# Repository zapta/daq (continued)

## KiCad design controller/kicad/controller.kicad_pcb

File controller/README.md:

# Data Acquisition - Controller board.

| :warning: WARNING                                               |
| :-------------------------------------------------------------- |
| This design is an unverified work in progress (as of May 2023). |

## Overview

This plugin board contains the microcontroller that controls the system and communicates with the host PC. It is based on the WeAct Studio STM32H750 module, and future version may have the STM32H750 MCU directly on the board.

## Design decisions

* All the MCU signals are routed to the bus, to provide flexibility and future system expansion.
* All signals are protected against ESD using TVS diodes.
* Controller can be powered from the bus or from the USB port, with power arbitration using OR'ed diodes. The USB power does not power the bus to avoid overloading the host computer.
* The WeAct module can be soldered to the board using pin header or can be removable using a set of male/female headers.

## Board dimensions

## BOM

Key components:

* WeAct Studio [STM32H750 module](https://github.com/WeActStudio/MiniSTM32H7xx).

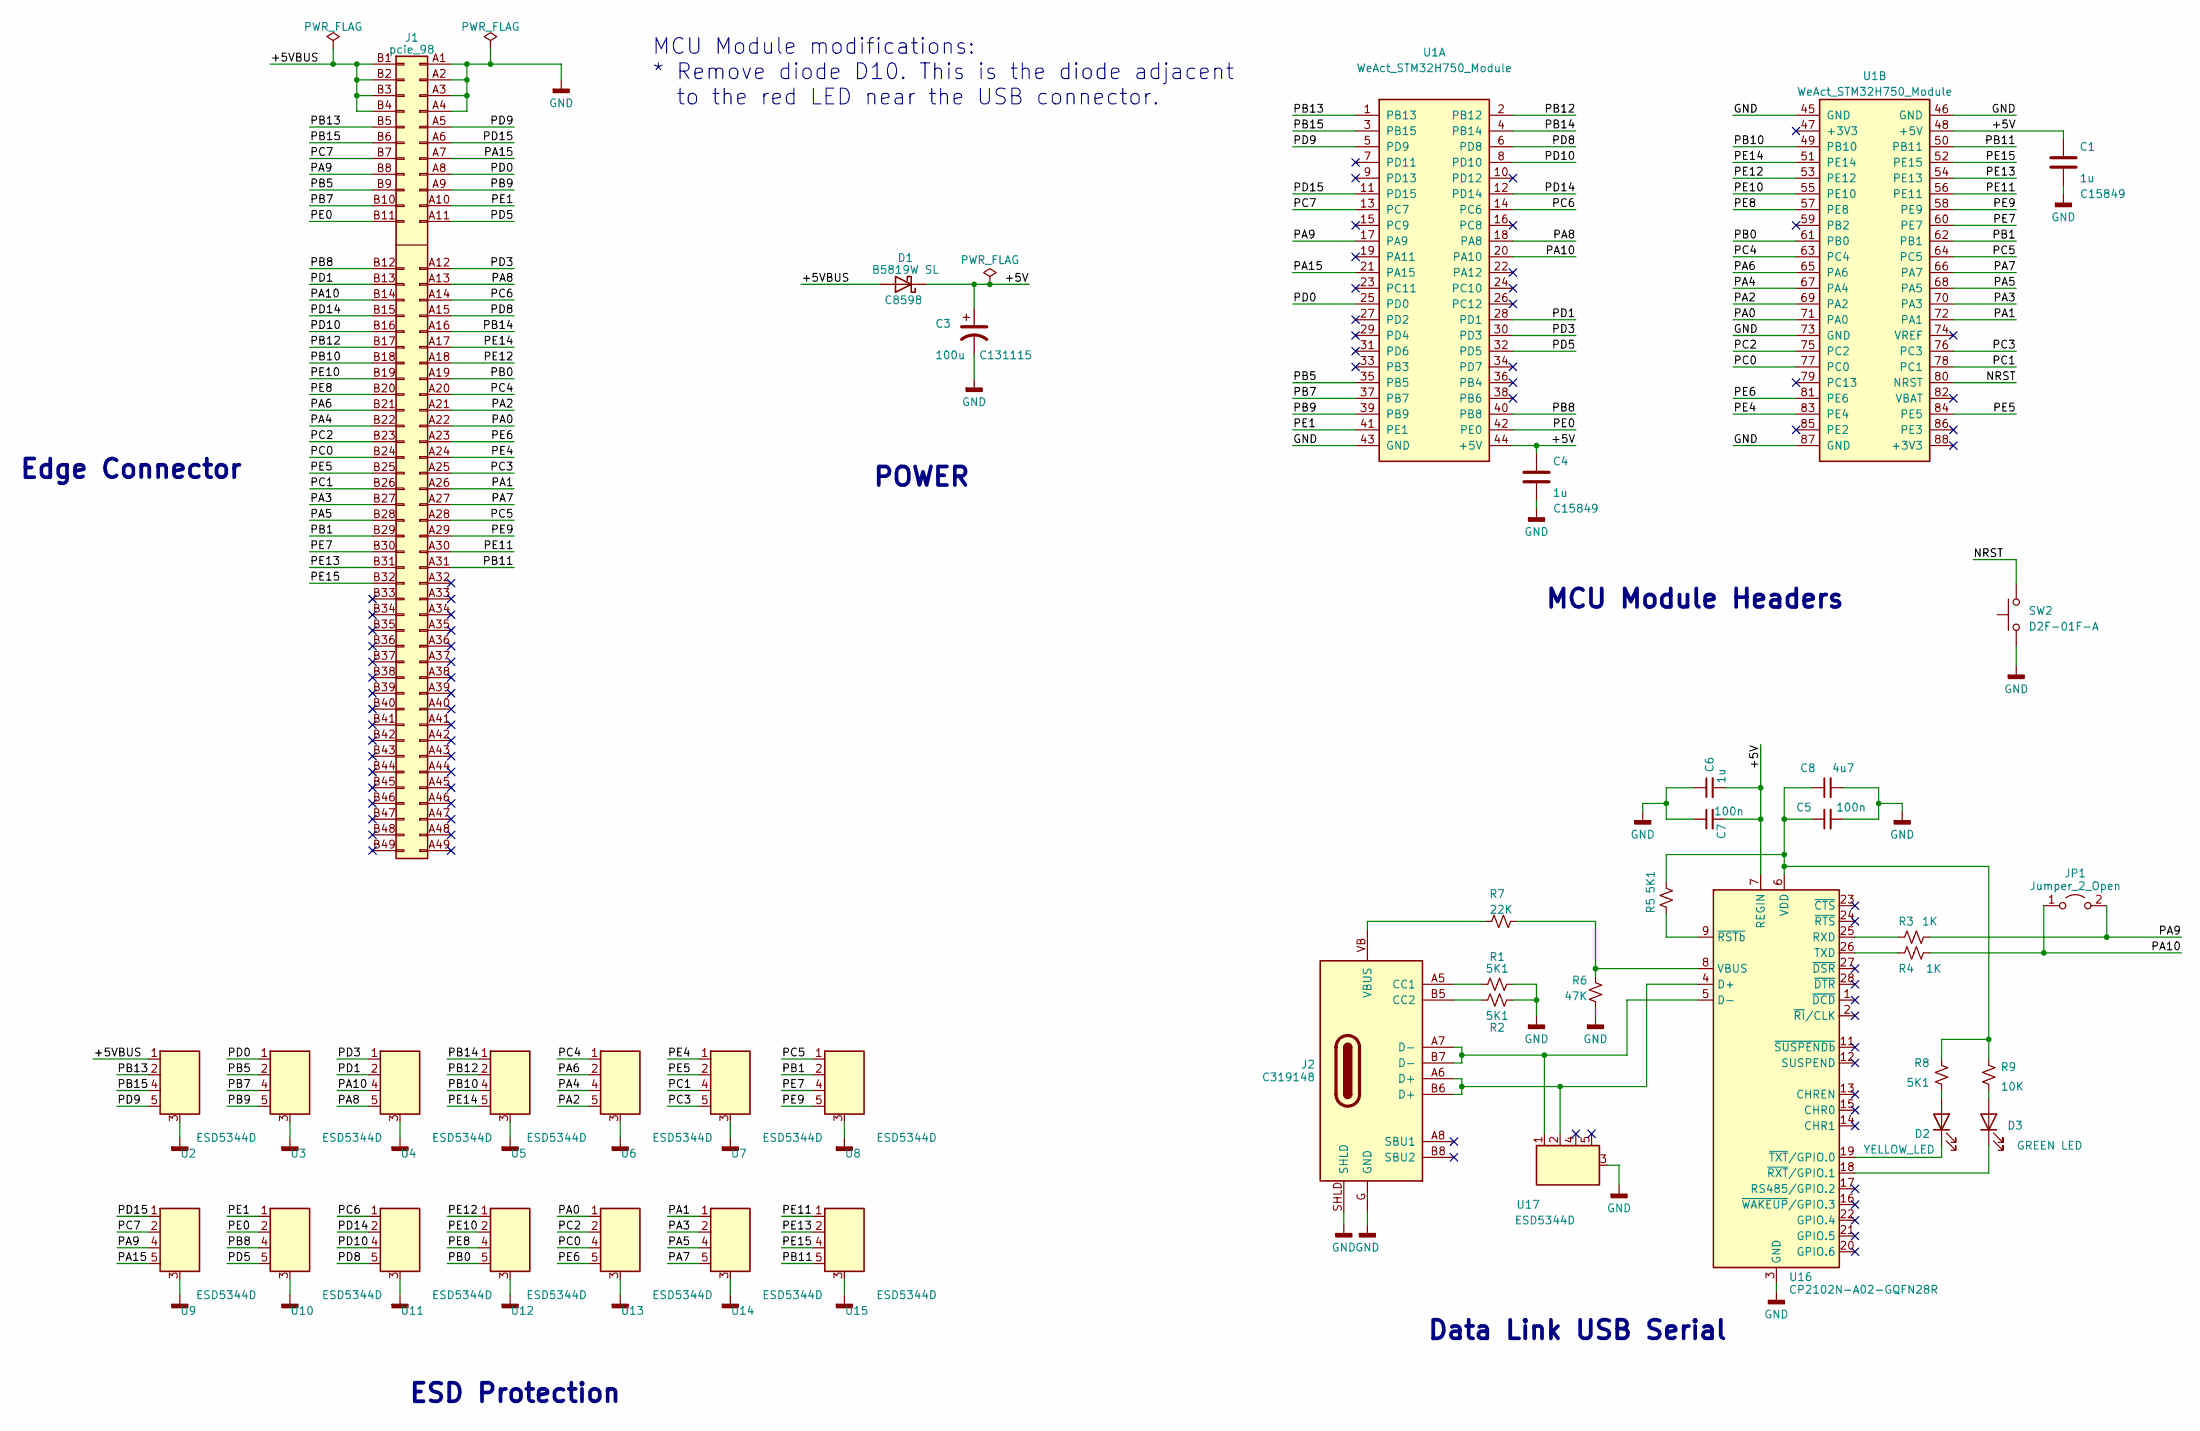
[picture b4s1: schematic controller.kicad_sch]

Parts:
C1, C4, C6: 1u; C_0603_1608Metric; LCSC C15849
C3: 100u; CP_Elec_5x5.4_JLCPCB; LCSC C131115
C5, C7: 100n; C_0603_1608Metric; LCSC C14663
C8: 4u7; C_0603_1608Metric; LCSC C19666
D1: B5819W SL; D_SOD-123; LCSC C8598
D2: YELLOW_LED; LED_0603_1608Metric; LCSC C72038
D3: GREEN LED; LED_0603_1608Metric; LCSC C72043
J1: pcie_98; PCIE_98_CARD; LCSC DNP
J2: USB_C_Receptacle_USB2.0; USB_C_Receptacle_XKB_U262-16XN-4BVC11; LCSC C319148
JP1: Jumper_2_Open; PinHeader_1x02_P2.54mm_Vertical; LCSC DNP
R1, R2, R5, R8: 5K1; R_0603_1608Metric; LCSC C23186
R3, R4: 1K; R_0603_1608Metric; LCSC C21190
R6: 47K; R_0603_1608Metric; LCSC C25819
R7: 22K; R_0603_1608Metric; LCSC C31850
R9: 10K; R_0603_1608Metric; LCSC C25804
SW2: D2F-01F-A; microswitch; LCSC C726013
U1: WeAct_STM32H750_Module; weact_stm32fh750; LCSC DNP
U2, U3, U4, U5, U6, U7, U8, U9, U10, U11, U12, U13, U14, U15, U17: ESD5344D; Diodes_UDFN-10_1.0x2.5mm_P0.5mm; LCSC C2841840
U16: CP2102N-A02-GQFN28R; QFN-28-1EP_5x5mm_P0.5mm_EP3.35x3.35mm; LCSC C964632

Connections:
/+5V: C1.1, C3.1, C4.1, C6.2, C7.2, D1.1 (K), U1.44 (+5V), U1.48 (+5V), U16.7 (REGIN)
/+5VBUS: D1.2 (A), J1.B1 (Pin_b1), J1.B2 (Pin_b2), J1.B3 (Pin_b3), J1.B4 (Pin_b4), U2.1 (D1)
/NRST: SW2.2, U1.80 (NRST)
/PA0: J1.A22 (Pin_a22), U1.71 (PA0), U13.1 (D1)
/PA1: J1.A26 (Pin_a26), U1.72 (PA1), U14.1 (D1)
/PA2: J1.A21 (Pin_a21), U1.69 (PA2), U6.5 (D4)
/PA3: J1.B27 (Pin_b27), U1.70 (PA3), U14.2 (D2)
/PA4: J1.B22 (Pin_b22), U1.67 (PA4), U6.4 (D3)
/PA5: J1.B28 (Pin_b28), U1.68 (PA5), U14.4 (D3)
/PA6: J1.B21 (Pin_b21), U1.65 (PA6), U6.2 (D2)
/PA7: J1.A27 (Pin_a27), U1.66 (PA7), U14.5 (D4)
/PA8: J1.A13 (Pin_a13), U1.18 (PA8), U4.5 (D4)
/PA9: J1.B8 (Pin_b8), JP1.2 (B), R3.2, U1.17 (PA9), U9.4 (D3)
/PA10: J1.B14 (Pin_b14), JP1.1 (A), R4.2, U1.20 (PA10), U4.4 (D3)
/PA15: J1.A7 (Pin_a7), U1.21 (PA15), U9.5 (D4)
/PB0: J1.A19 (Pin_a19), U1.61 (PB0), U12.5 (D4)
/PB1: J1.B29 (Pin_b29), U1.62 (PB1), U8.2 (D2)
/PB5: J1.B9 (Pin_b9), U1.35 (PB5), U3.2 (D2)
/PB7: J1.B10 (Pin_b10), U1.37 (PB7), U3.4 (D3)
/PB8: J1.B12 (Pin_b12), U1.40 (PB8), U10.4 (D3)
/PB9: J1.A9 (Pin_a9), U1.39 (PB9), U3.5 (D4)
/PB10: J1.B18 (Pin_b18), U1.49 (PB10), U5.4 (D3)
/PB11: J1.A31 (Pin_a31), U1.50 (PB11), U15.5 (D4)
/PB12: J1.B17 (Pin_b17), U1.2 (PB12), U5.2 (D2)
/PB13: J1.B5 (Pin_b5), U1.1 (PB13), U2.2 (D2)
/PB14: J1.A16 (Pin_a16), U1.4 (PB14), U5.1 (D1)
/PB15: J1.B6 (Pin_b6), U1.3 (PB15), U2.4 (D3)
/PC0: J1.B24 (Pin_b24), U1.77 (PC0), U13.4 (D3)
/PC1: J1.B26 (Pin_b26), U1.78 (PC1), U7.4 (D3)
/PC2: J1.B23 (Pin_b23), U1.75 (PC2), U13.2 (D2)
/PC3: J1.A25 (Pin_a25), U1.76 (PC3), U7.5 (D4)
/PC4: J1.A20 (Pin_a20), U1.63 (PC4), U6.1 (D1)
/PC5: J1.A28 (Pin_a28), U1.64 (PC5), U8.1 (D1)
/PC6: J1.A14 (Pin_a14), U1.14 (PC6), U11.1 (D1)
/PC7: J1.B7 (Pin_b7), U1.13 (PC7), U9.2 (D2)
/PD0: J1.A8 (Pin_a8), U1.25 (PD0), U3.1 (D1)
/PD1: J1.B13 (Pin_b13), U1.28 (PD1), U4.2 (D2)
/PD3: J1.A12 (Pin_a12), U1.30 (PD3), U4.1 (D1)
/PD5: J1.A11, U1.32 (PD5), U10.5 (D4)
/PD8: J1.A15 (Pin_a15), U1.6 (PD8), U11.5 (D4)
/PD9: J1.A5 (Pin_a5), U1.5 (PD9), U2.5 (D4)
/PD10: J1.B16 (Pin_b16), U1.8 (PD10), U11.4 (D3)
/PD14: J1.B15 (Pin_b15), U1.12 (PD14), U11.2 (D2)
/PD15: J1.A6 (Pin_a6), U1.11 (PD15), U9.1 (D1)
/PE0: J1.B11 (Pin_b11), U1.42 (PE0), U10.2 (D2)
/PE1: J1.A10 (Pin_a10), U1.41 (PE1), U10.1 (D1)
/PE4: J1.A24 (Pin_a24), U1.83 (PE4), U7.1 (D1)
/PE5: J1.B25 (Pin_b25), U1.84 (PE5), U7.2 (D2)
/PE6: J1.A23 (Pin_a23), U1.81 (PE6), U13.5 (D4)
/PE7: J1.B30 (Pin_b30), U1.60 (PE7), U8.4 (D3)
/PE8: J1.B20 (Pin_b20), U1.57 (PE8), U12.4 (D3)
/PE9: J1.A29 (Pin_a29), U1.58 (PE9), U8.5 (D4)
/PE10: J1.B19 (Pin_b19), U1.55 (PE10), U12.2 (D2)
/PE11: J1.A30 (Pin_a30), U1.56 (PE11), U15.1 (D1)
/PE12: J1.A18 (Pin_a18), U1.53 (PE12), U12.1 (D1)
/PE13: J1.B31 (Pin_b31), U1.54 (PE13), U15.2 (D2)
/PE14: J1.A17 (Pin_a17), U1.51 (PE14), U5.5 (D4)
/PE15: J1.B32 (Pin_b32), U1.52 (PE15), U15.4 (D3)
GND: C1.2, C3.2, C4.2, C5.2, C6.1, C7.1, C8.2, J1.A1 (Pin_a1), J1.A2 (Pin_a2), J1.A3 (Pin_a3), J1.A4 (Pin_a4), J2.G (GND), J2.SHLD, R1.2, R2.2, R6.1, SW2.1, U1.43 (GND), U1.45 (GND), U1.46 (GND), U1.73 (GND), U1.87 (GND), U2.3 (GND), U3.3 (GND), U4.3 (GND), U5.3 (GND), U6.3 (GND), U7.3 (GND), U8.3 (GND), U9.3 (GND), U10.3 (GND), U11.3 (GND), U12.3 (GND), U13.3 (GND), U14.3 (GND), U15.3 (GND), U16.3 (GND), U16.29 (GND), U17.3 (GND)
unnamed: D2.2 (A), R8.1
unnamed: D2.1 (K), U16.19 (~TXT/GPIO.0)
unnamed: D3.2 (A), R9.1
unnamed: D3.1 (K), U16.18 (~RXT/GPIO.1)
unnamed: J2.A5 (CC1), R1.1
unnamed: J2.B5 (CC2), R2.1
unnamed: J2.VB (VBUS), R7.2
unnamed: J2.A6 (D+), J2.B6 (D+), U16.4 (D+), U17.2 (D2)
unnamed: J2.A7 (D-), J2.B7 (D-), U16.5 (D-), U17.1 (D1)
unnamed: R3.1, U16.25 (RXD)
unnamed: R4.1, U16.26 (TXD)
unnamed: R6.2, R7.1, U16.8 (VBUS)
unnamed: C5.1, C8.1, R5.2, R8.2, R9.2, U16.6 (VDD)
unnamed: R5.1, U16.9 (~RSTb)

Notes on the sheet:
ESD Protection
MCU Module Headers
Data Link USB Serial
Edge Connector
POWER
MCU Module modifications: * Remove diode D10. This is the diode adjacent to the red LED near the USB connector.

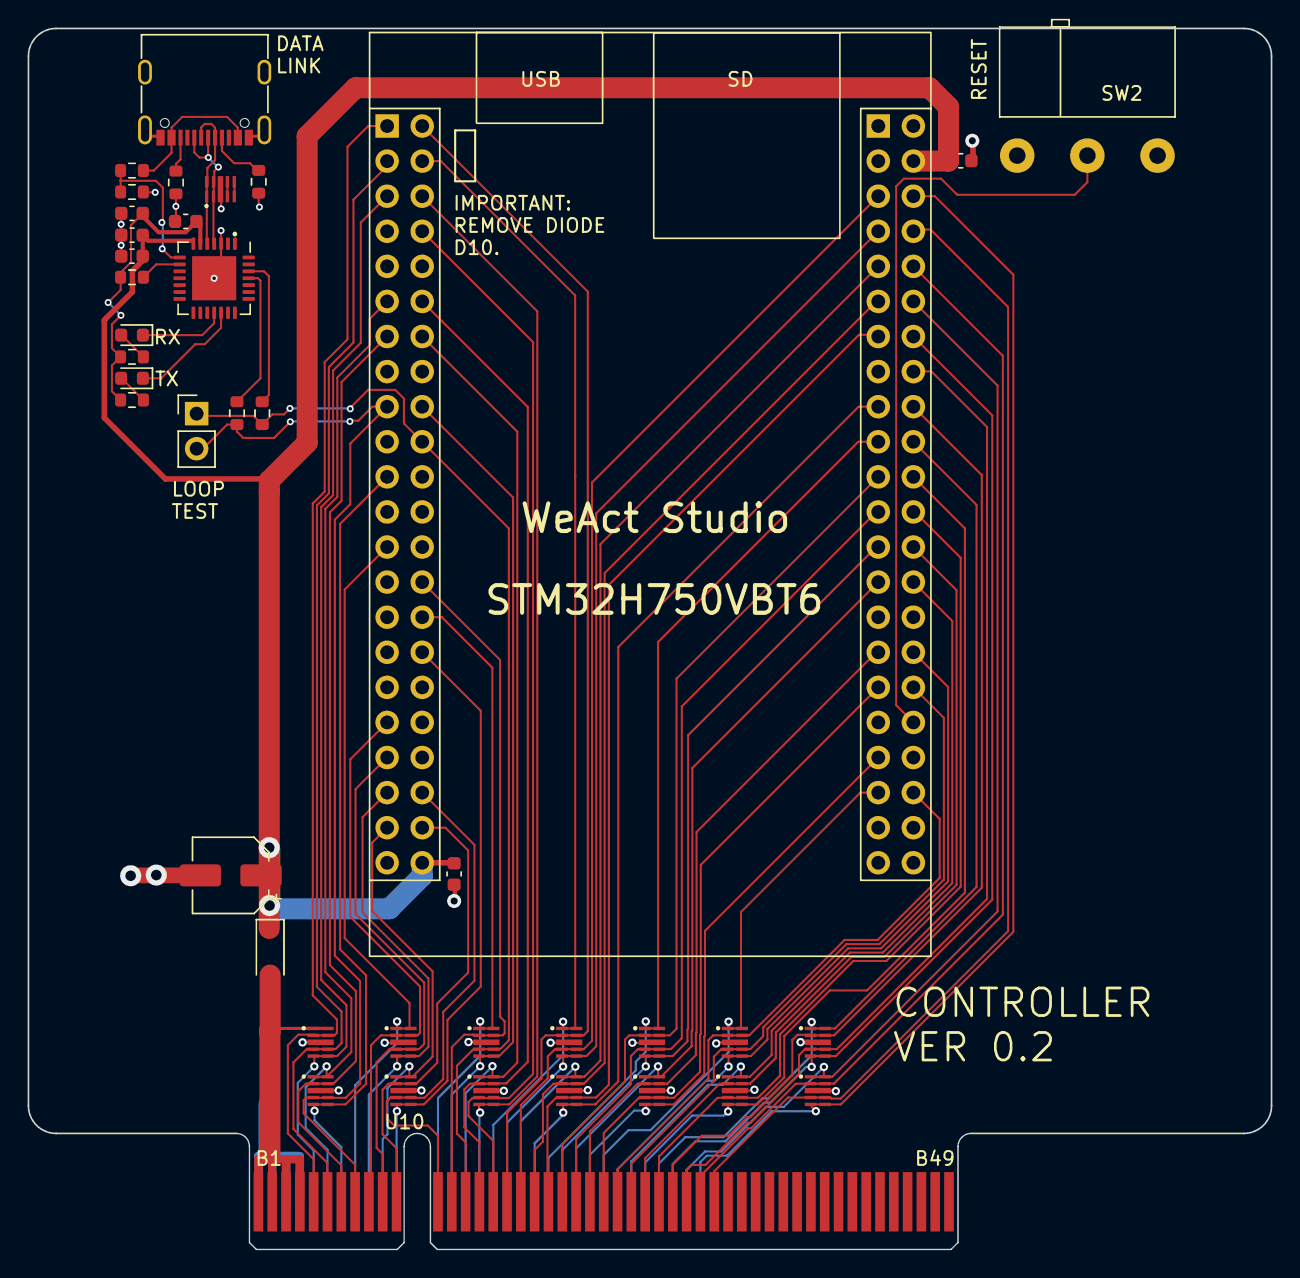
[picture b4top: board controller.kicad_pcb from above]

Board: 2 copper layers, 90.0 x 88.4 mm, 40 parts (0 on the bottom side), 73 nets.

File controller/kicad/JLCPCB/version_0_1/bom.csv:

Designator,Footprint,Quantity,Value,LCSC Part #
"C1, C4, C6",0603,3,1u,C15849
"C2, C3",CP_Elec_5x5.4_JLCPCB,2,100u,C131115
"C5, C7",0603,2,100n,C14663
C8,0603,1,4u7,C19666
D1,D_SOD-123,1,B5819W SL,C8598
J1,PCIE_98_CARD,1,pcie_98,DNP
J2,USB_C_Receptacle_XKB_U262-16XN-4BVC11,1,USB_C_Receptacle_USB2.0,C319148
JP1,PinHeader_1x02_P2.54mm_Vertical,1,Jumper_2_Open,DNP
"R1, R2, R5",0603,3,5K1,C23186
"R3, R4",0603,2,1K,C21190
U1,weact_stm32fh750,1,WeAct_STM32H750_Module,DNP
"U10, U11, U12, U13, U14, U15, U2, U3, U4, U5, U6, U7, U8, U9",Diodes_UDFN-10_1.0x2.5mm_P0.5mm,14,ESD5344D,C2841840
U16,QFN-28-1EP_5x5mm_P0.5mm_EP3.35x3.35mm,1,CP2102N-A01-GQFN28-Interface_USB,C6568

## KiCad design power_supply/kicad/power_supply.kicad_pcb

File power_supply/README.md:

# Data Acquisition - Power Supply board.

| :warning: WARNING|
|:---|
| This design is an unverified work in progress (as of May 2023).|

## Overview

This plugin board contains an DC/DC module which generates the 5VCD feed of the bus from the 12-24V DC input.

## Design decisions

* The power supply is isolated such that VIN is not galvanically connected to the system.
* Can provide 5V @ 2A from 9-36VDC input.
* Contains fuses on input and output voltages and ESD protection on the 5V output voltage.
* Contains indication LEDs for input and output voltages.
* Contains test points for input and output voltages.
* Inexpensive 2 layers PCB design with one layer dedicated for ground plane.
* Not intended for hot swapping.

## Board dimensions

Identical to the controller board.

## BOM

* URB2405YMD-10WR3 DC/DC module. Available from several vendors, with  
Mornsun being the canonical one.

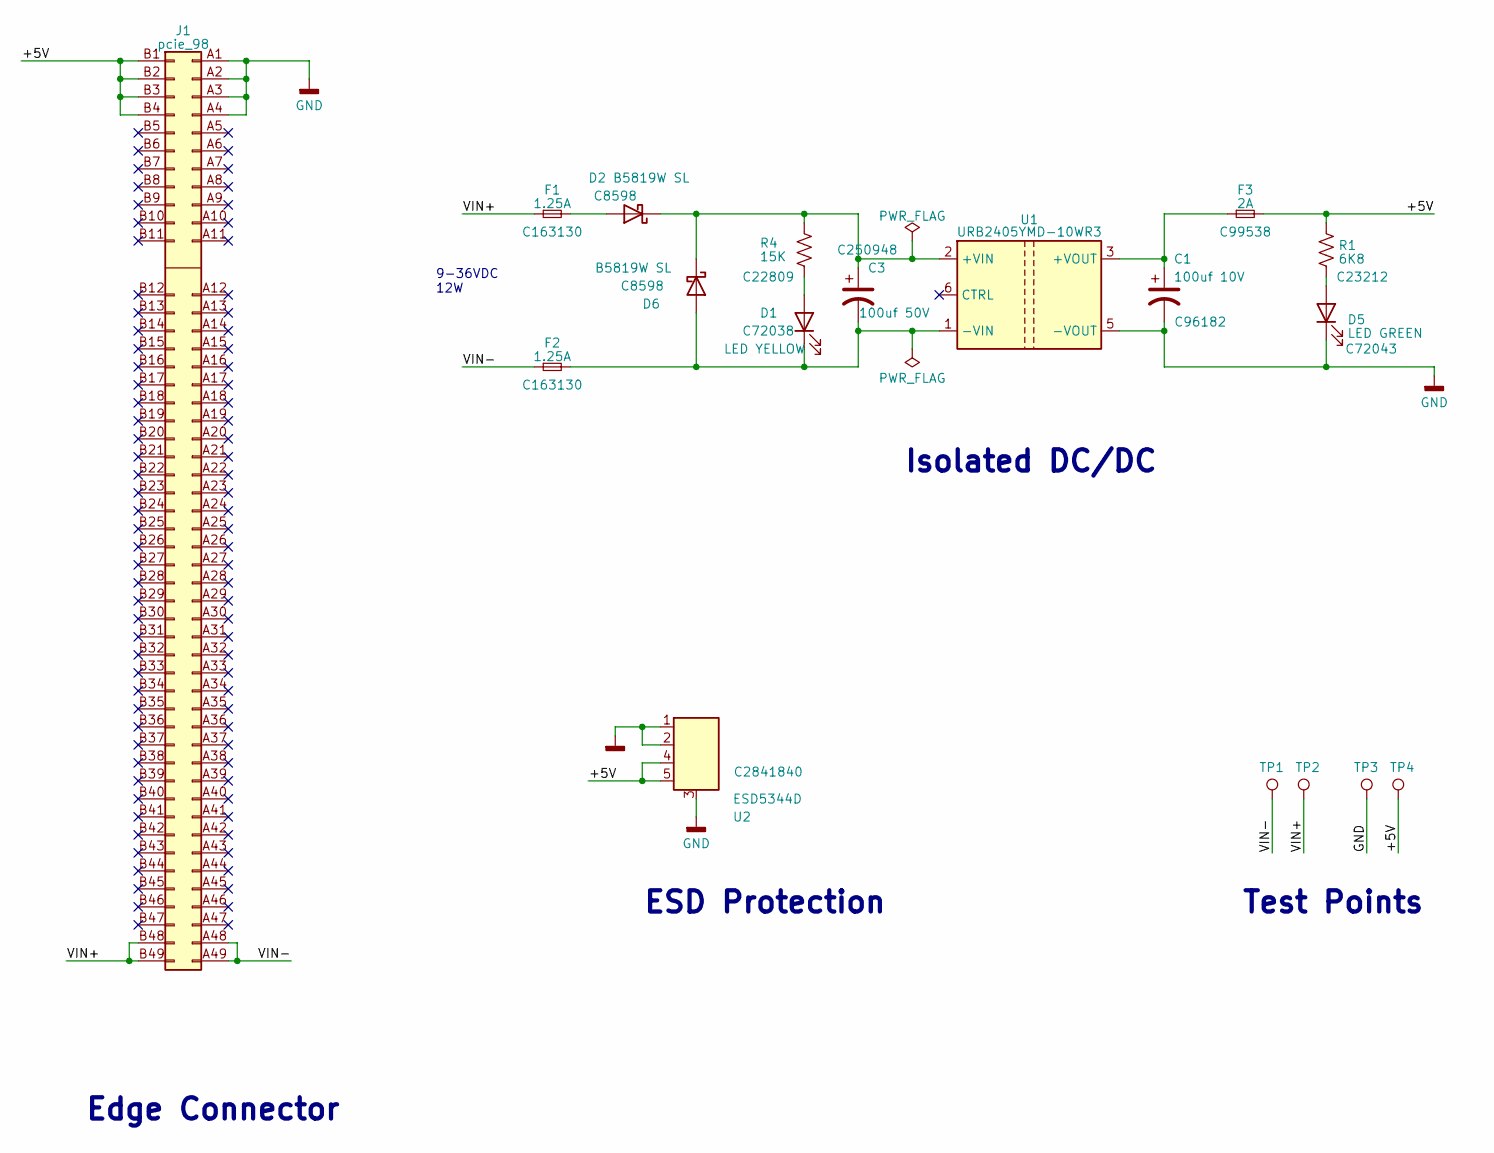
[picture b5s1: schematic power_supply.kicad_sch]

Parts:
C1: 100uf 10V; CP_Elec_5x5.4; LCSC C96182
C3: 100uf 50V; C_Elec_8x10.2; LCSC C250948
D1: LED YELLOW; LED_0603_1608Metric; LCSC C72038
D2, D6: B5819W SL; D_SOD-123; LCSC C8598
D5: LED GREEN; LED_0603_1608Metric; LCSC C72043
F1, F2: 1.25A; Fuse_1206_3216Metric_Pad1.42x1.75mm_HandSolder; LCSC C163130
F3: 2A; Fuse_1206_3216Metric_Pad1.42x1.75mm_HandSolder; LCSC C99538
J1: pcie_98; PCIE_98_CARD; LCSC DNP
R1: 6K8; R_0603_1608Metric; LCSC C23212
R4: 15K; R_0603_1608Metric; LCSC C22809
TP1, TP2, TP3, TP4: TestPoint; Test_Pad; LCSC DNP
U1: URB2405YMD-10WR3; DCDC; LCSC C91825
U2: ESD5344D; Diodes_UDFN-10_1.0x2.5mm_P0.5mm; LCSC C2841840

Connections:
/+5V: F3.2, J1.B1 (Pin_b1), J1.B2 (Pin_b2), J1.B3 (Pin_b3), J1.B4 (Pin_b4), R1.1, TP4.1, U2.4 (D3), U2.5 (D4)
/VIN+: F1.1, J1.B48 (Pin_b48), J1.B49 (Pin_b49), TP2.1
/VIN-: F2.1, J1.A48 (Pin_a48), J1.A49 (Pin_a49), TP1.1
GND: C1.2, D5.1 (K), J1.A1 (Pin_a1), J1.A2 (Pin_a2), J1.A3 (Pin_a3), J1.A4 (Pin_a4), TP3.1, U1.5 (-VOUT), U2.1 (D1), U2.2 (D2), U2.3 (GND)
unnamed: D1.2 (A), R4.2
unnamed: C3.2, D1.1 (K), D6.2 (A), F2.2, U1.1 (-VIN)
unnamed: D2.2 (A), F1.2
unnamed: C3.1, D2.1 (K), D6.1 (K), R4.1, U1.2 (+VIN)
unnamed: D5.2 (A), R1.2
unnamed: C1.1, F3.1, U1.3 (+VOUT)

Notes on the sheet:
ESD Protection
9-36VDC 12W
Edge Connector
Isolated DC/DC
Test Points

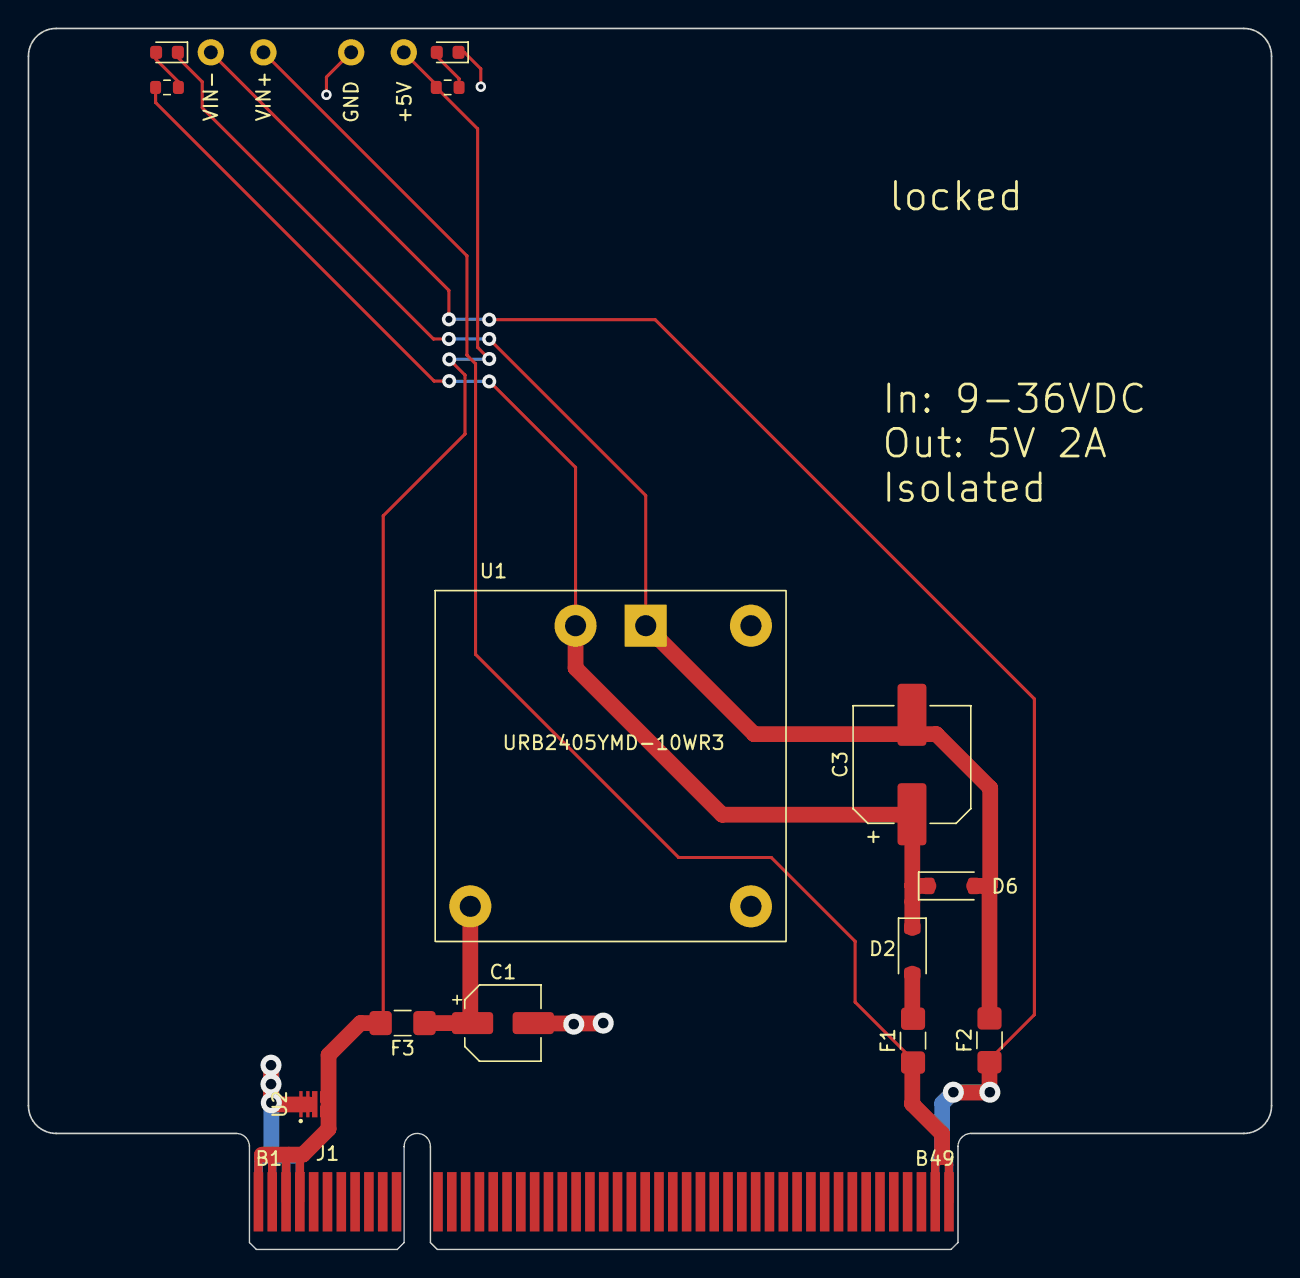
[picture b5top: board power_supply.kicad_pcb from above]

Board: 2 copper layers, 90.0 x 88.4 mm, 18 parts (0 on the bottom side), 10 nets.
